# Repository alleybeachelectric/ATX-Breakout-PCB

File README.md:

# ATX-Breakout-PCB
ATX power supply adapter that has fuses, banana connectors for 12v, 5v, 3v3, -5v, -12v, and gnd. will have LCD display for for each voltage output (hopefully OLED or multidigit 7 seg displays)

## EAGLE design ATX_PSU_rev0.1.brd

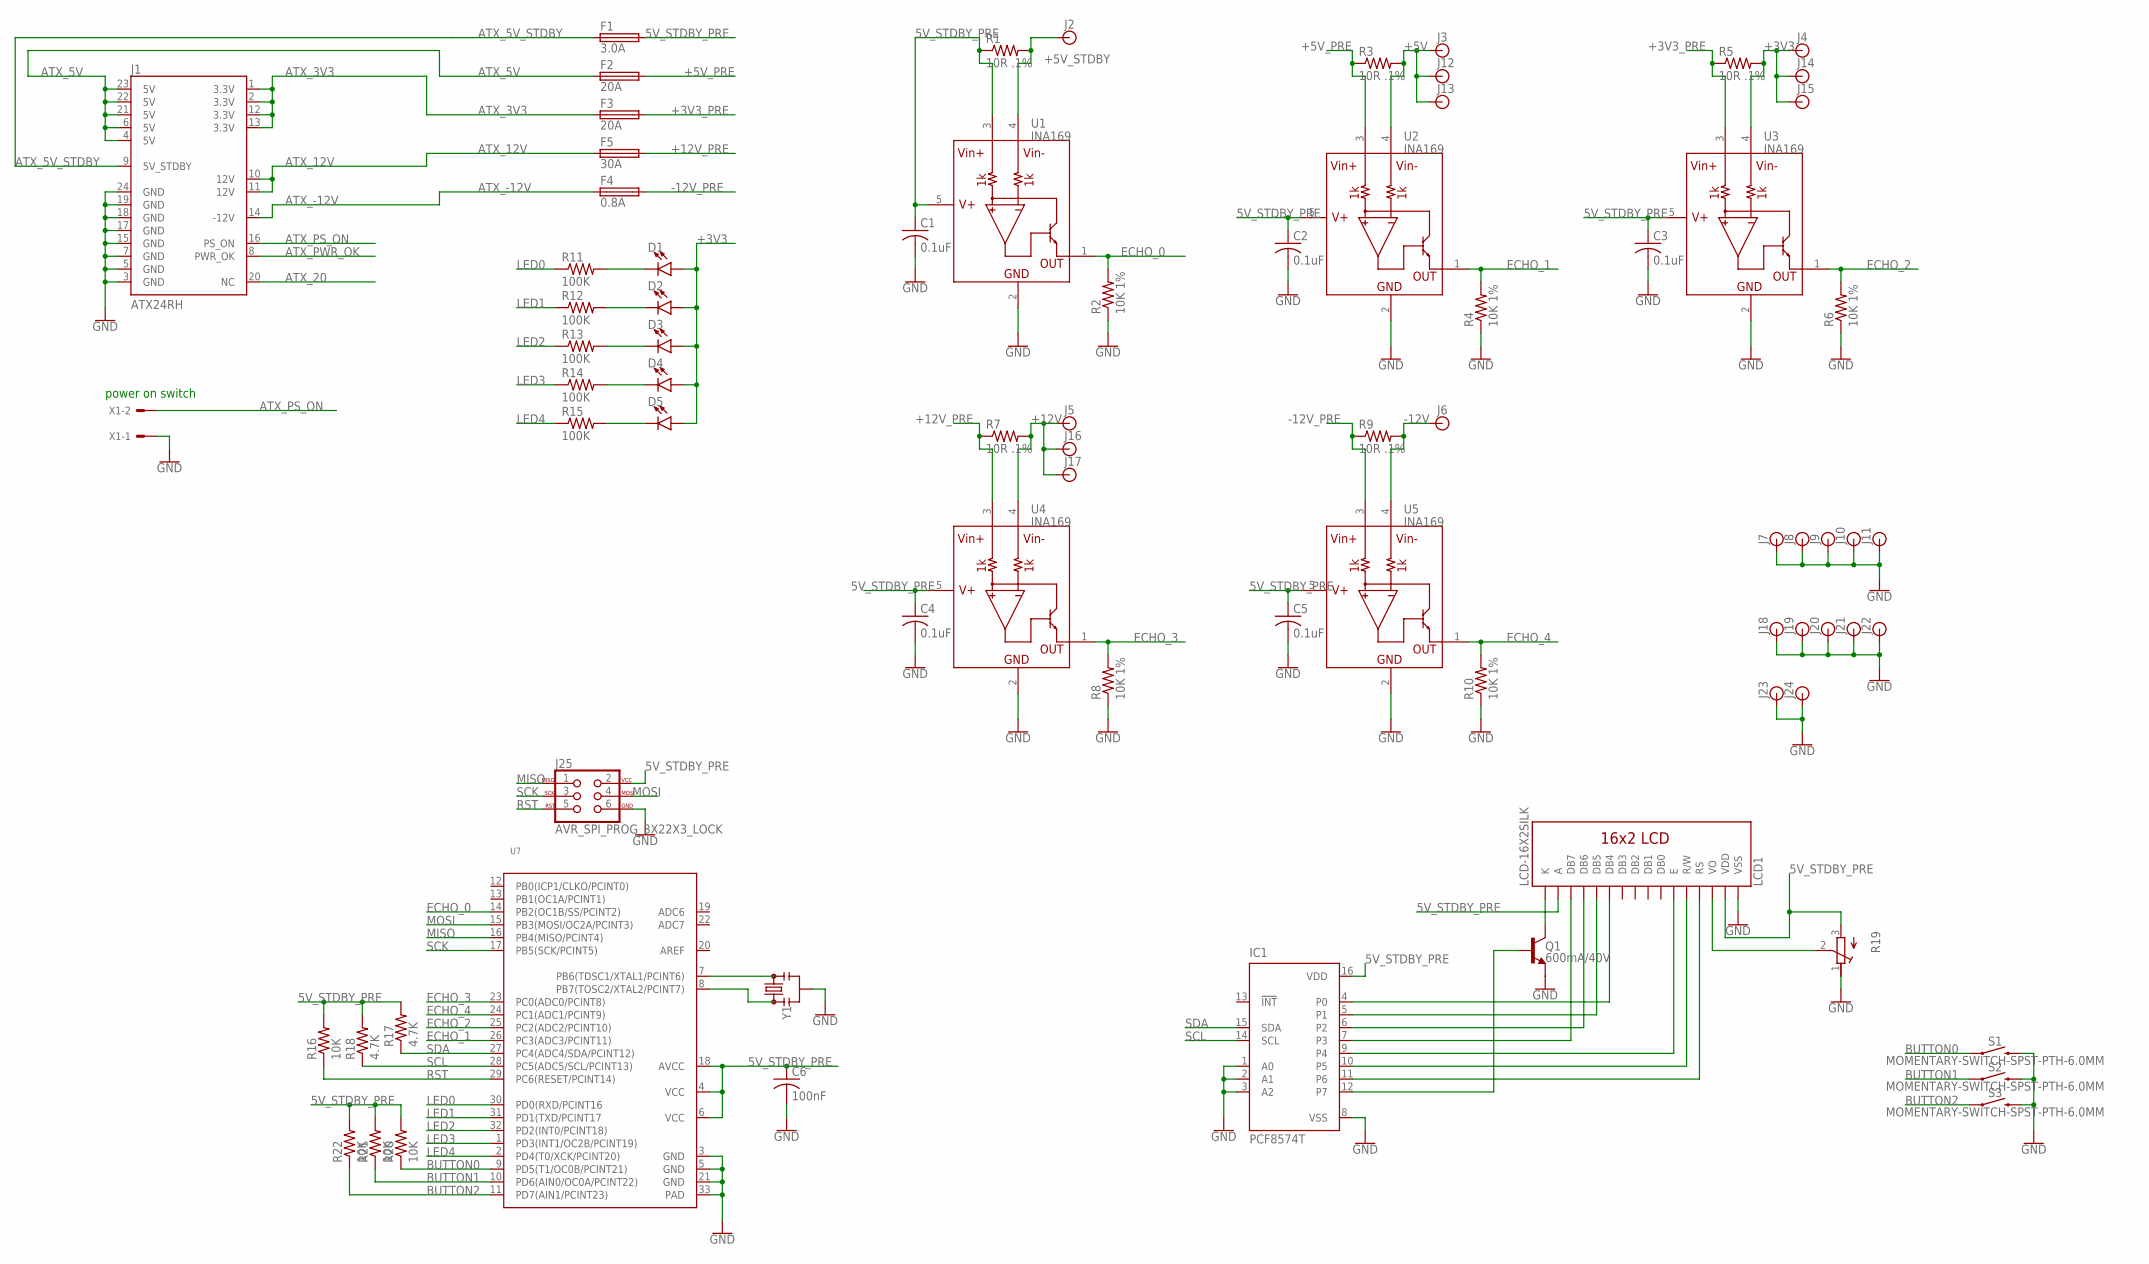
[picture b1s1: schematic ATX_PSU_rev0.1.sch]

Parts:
C1, C2, C3, C4, C5: 0.1uF; C1206
C6: 100nF; C1206
D1, D2, D3, D4, D5: LED-FKIT-1206; FKIT-LED-1206
F1: 3.0A; FUSE_HOLDER_5X20MM
F2, F3: 20A; FUSE_HOLDER_5X20MM
F4: 0.8A; FUSE_HOLDER_5X20MM
F5: 30A; FUSE_HOLDER_5X20MM
IC1: PCF8574T; SO16W
J1: ATX24RH; ATX24_RIGHT_ANGLE
J2, J3, J4, J5, J6, J7, J8, J9, J10, J11, J12, J13, J14, J15, J16, J17, J18, J19, J20, J21, J22, J23, J24: BANANA_CONN
J25: AVR_SPI_PROG_3X22X3_LOCK; 2X3_LOCK
LCD1: LCD-16X2SILK; LCD-16X2
Q1: 600mA/40V; SOT23-3
R1, R3, R5, R7, R9: 10R .1%; R1206
R2, R4, R6, R8, R10: 10K 1%; R1206
R11, R12, R13, R14, R15: 100K; R1206
R16, R20, R21, R22: 10K; R1206
R17, R18: 4.7K; R1206
R19: R-TRIMM3314G; RTRIM3314G
S1, S2, S3: MOMENTARY-SWITCH-SPST-PTH-6.0MM; TACTILE_SWITCH_PTH_6.0MM
U1, U2, U3, U4, U5: INA169; SOT23-5
U7: MCU-ATMEGA168PA-MU(QFN32); QFN32G-0.5-5X5MM
X1: KK-156-2
Y1: RESONATORSMD-3.2X1.3; RESONATOR-SMD-3.2X1.3

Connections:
5V_STDBY_PRE: C1.1, C2.1, C3.1, C4.1, C5.1, C6.1, F1.2, IC1.16 (VDD), J25.2, LCD1.2 (VDD), LCD1.15 (A), R1.1, R16.2, R17.2, R18.2, R19.3 (A), R20.2, R21.2, R22.2, U1.3 (VIN+), U1.5 (V+), U2.5 (V+), U3.5 (V+), U4.5 (V+), U5.5 (V+), U7.4 (VCC), U7.6 (VCC), U7.18 (AVCC)
+3V3: D1.A, D2.A, D3.A, D4.A, D5.A, J4.P$1, J14.P$1, J15.P$1, R5.2, U3.4 (VIN-)
+3V3_PRE: F3.2, R5.1, U3.3 (VIN+)
+5V: J3.P$1, J12.P$1, J13.P$1, R3.2, U2.4 (VIN-)
+5V_PRE: F2.2, R3.1, U2.3 (VIN+)
+5V_STDBY: J2.P$1, R1.2, U1.4 (VIN-)
+12V: J5.P$1, J16.P$1, J17.P$1, R7.2, U4.4 (VIN-)
+12V_PRE: F5.2, R7.1, U4.3 (VIN+)
-12V: J6.P$1, R9.2, U5.4 (VIN-)
-12V_PRE: F4.2, R9.1, U5.3 (VIN+)
ATX_3V3: F3.1, J1.1 (3.3V), J1.2 (3.3V), J1.12 (3.3V), J1.13 (3.3V)
ATX_5V: F2.1, J1.4 (5V), J1.6 (5V), J1.21 (5V), J1.22 (5V), J1.23 (5V)
ATX_5V_STDBY: F1.1, J1.9 (5V_STDBY)
ATX_12V: F5.1, J1.10 (12V), J1.11 (12V)
ATX_20: J1.20 (NC)
ATX_-12V: F4.1, J1.14 (-12V)
ATX_PS_ON: J1.16 (PS_ON), X1.2
ATX_PWR_OK: J1.8 (PWR_OK)
BUTTON0: R20.1, S1.1, U7.9 (PD5(T1/OC0B/PCINT21))
BUTTON1: R21.1, S2.1, U7.10 (PD6(AIN0/OC0A/PCINT22))
BUTTON2: R22.1, S3.1, U7.11 (PD7(AIN1/PCINT23))
ECHO_0: R2.2, U1.1 (OUT), U7.14 (PB2(OC1B/SS/PCINT2))
ECHO_1: R4.2, U2.1 (OUT), U7.26 (PC3(ADC3/PCINT11))
ECHO_2: R6.2, U3.1 (OUT), U7.25 (PC2(ADC2/PCINT10))
ECHO_3: R8.2, U4.1 (OUT), U7.23 (PC0(ADC0/PCINT8))
ECHO_4: R10.2, U5.1 (OUT), U7.24 (PC1(ADC1/PCINT9))
GND: C1.2, C2.2, C3.2, C4.2, C5.2, C6.2, IC1.1 (A0), IC1.2 (A1), IC1.3 (A2), IC1.8 (VSS), J1.3 (GND), J1.5 (GND), J1.7 (GND), J1.15 (GND), J1.17 (GND), J1.18 (GND), J1.19 (GND), J1.24 (GND), J7.P$1, J8.P$1, J9.P$1, J10.P$1, J11.P$1, J18.P$1, J19.P$1, J20.P$1, J21.P$1, J22.P$1, J23.P$1, J24.P$1, J25.6, LCD1.1 (VSS), Q1.2 (E), R2.1, R4.1, R6.1, R8.1, R10.1, R19.1 (E), S1.3 (2), S2.3 (2), S3.3 (2), U1.2 (GND), U2.2 (GND), U3.2 (GND), U4.2 (GND), U5.2 (GND), U7.3 (GND), U7.5 (GND), U7.21 (GND), U7.33 (PAD), X1.1, Y1.2
LED0: R11.1, U7.30 (PD0(RXD/PCINT16)
LED1: R12.1, U7.31 (PD1(TXD/PCINT17)
LED2: R13.1, U7.32 (PD2(INT0/PCINT18))
LED3: R14.1, U7.1 (PD3(INT1/OC2B/PCINT19))
LED4: R15.1, U7.2 (PD4(T0/XCK/PCINT20))
MISO: J25.1, U7.16 (PB4(MISO/PCINT4))
MOSI: J25.4, U7.15 (PB3(MOSI/OC2A/PCINT3))
unnamed: D1.C, R11.2
unnamed: D2.C, R12.2
unnamed: IC1.4 (P0), LCD1.11 (DB4)
unnamed: D3.C, R13.2
unnamed: D4.C, R14.2
unnamed: D5.C, R15.2
unnamed: IC1.5 (P1), LCD1.12 (DB5)
unnamed: U7.8 (PB7(TOSC2/XTAL2/PCINT7)), Y1.1
unnamed: IC1.6 (P2), LCD1.13 (DB6)
unnamed: IC1.7 (P3), LCD1.14 (DB7)
unnamed: U7.7 (PB6(TDSC1/XTAL1/PCINT6)), Y1.3
unnamed: IC1.9 (P4), LCD1.6 (E)
unnamed: IC1.10 (P5), LCD1.5 (R/W)
unnamed: IC1.11 (P6), LCD1.4 (RS)
unnamed: IC1.12 (P7), Q1.1 (B)
unnamed: LCD1.16 (K), Q1.3 (C)
unnamed: LCD1.3 (VO), R19.2 (S)
RST: J25.5, R16.1, U7.29 (PC6(RESET/PCINT14))
SCK: J25.3, U7.17 (PB5(SCK/PCINT5))
SCL: IC1.14 (SCL), R18.1, U7.28 (PC5(ADC5/SCL/PCINT13))
SDA: IC1.15 (SDA), R17.1, U7.27 (PC4(ADC4/SDA/PCINT12))

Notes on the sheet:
power on switch

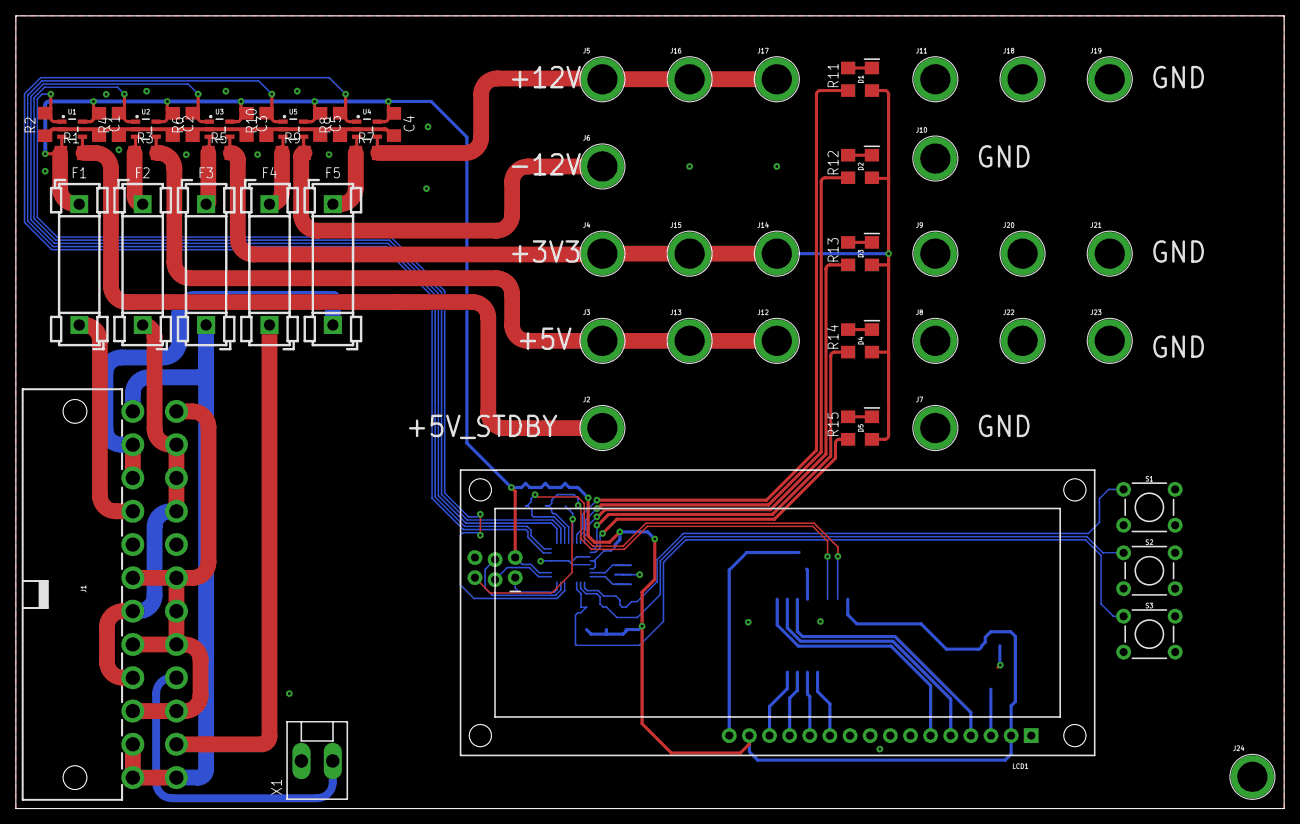
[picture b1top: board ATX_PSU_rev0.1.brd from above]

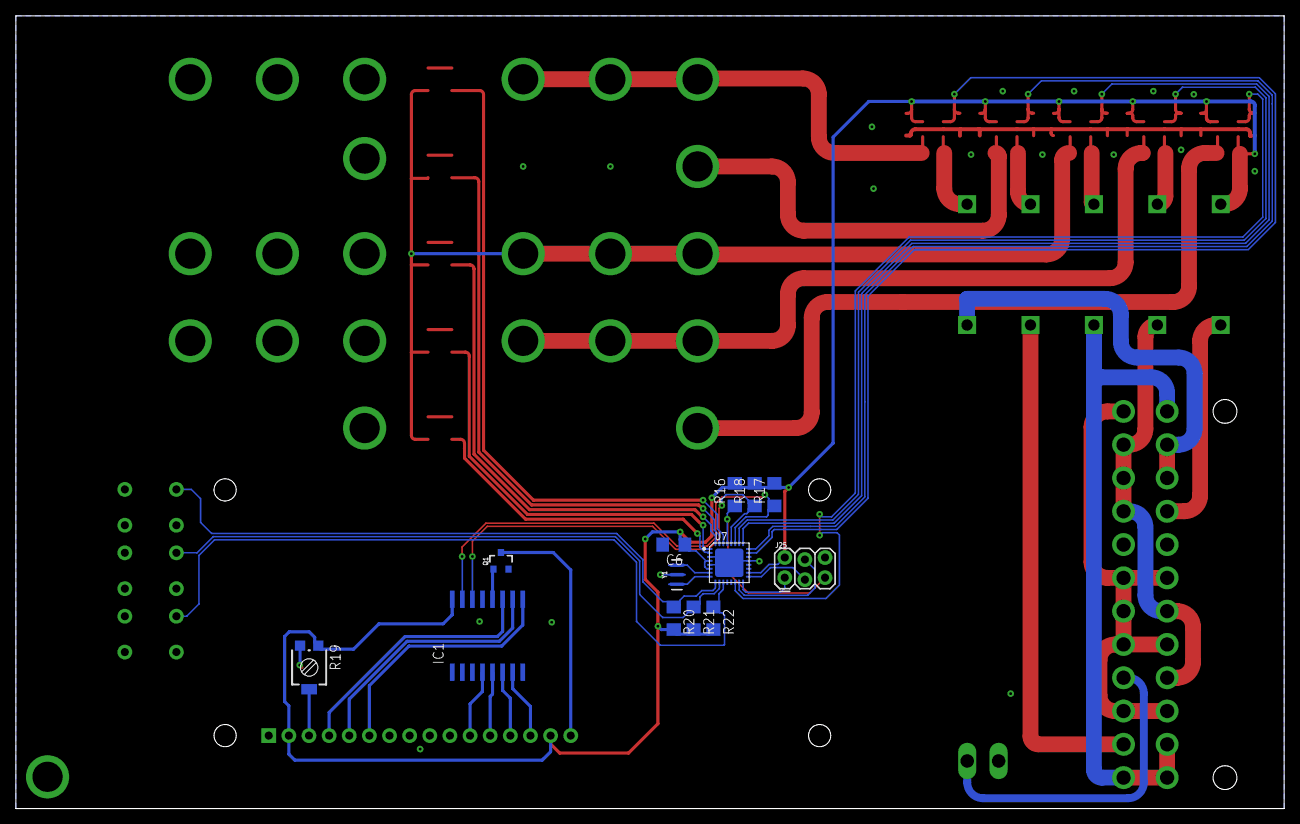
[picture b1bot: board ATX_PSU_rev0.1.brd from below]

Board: 2 copper layers, 160.0 x 100.0 mm, 77 parts (13 on the bottom side), 53 nets.

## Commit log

2018-07-27 added text
2018-07-28 added INA169's to design. need to add a microcontroller (atmega328 or similar) and chose a display. need to source a switch and a few buttons for menu. added LED;s for PGOOD
2018-08-03 added microcontroller
    made some connections to microcontroller.
2018-08-07 added some parts
    LCD with I2C backpack and 3 buttons.
    I belive routing is finished, but I want to reroute using polygons for large connectors, and figure out how this will be enclosed.

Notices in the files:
parts and their libraries:
SparkFun-Connectors: Licensing: Creative Commons ShareAlike 4.0 International - https://creativecommons.org/licenses/by-sa/4.0
